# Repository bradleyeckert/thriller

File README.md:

# FPGA security stack with ROT

Root of trust for an FPGA-based device platform, built from three parts: an FPGA with an encrypted and authenticated bitstream,
one QSPI NOR flash, and a TPM 2.0 (ST33KTPM2X). The FPGA is a model of the ASIC that replaces it
at volume (`doc/ics55.md`), so everything the FPGA does is generic RTL and firmware, and everything that depends on the FPGA family lives in `fpga/<family>/`.

- **The FPGA is the root of trust and the application.** Its configuration engine authenticates and decrypts the bitstream with the device's own eFuse key;
  the bitstream holds a boot ROM, a loader core that owns every key path and security decision and is, with its hardware, the FIPS 140-3 cryptographic module; a supervisor core that
  runs the manufacturer's transports, scheduling and CLI outside the module, so that those change without a CMVP filing; and an application core that runs the LiteForth application and can reach
  nothing secret. All three execute in place from the flash through a decrypting, authenticating cache (`doc/xip.md`).
- **The TPM holds what must survive the bitstream:** the device's keys, its identity, and the two monotonic counters that stop rollback.
  It releases a key only to a bitstream that holds the current pairing key, and the data key only after the host has proved itself to the TPM directly (`doc/tpm.md`).
  It is a FIPS 140-3 validated module in its own right, which is what lets the device's own module boundary stop at the loader domain (`doc/fips.md`).
- **The flash is untrusted storage** for the bitstream, the loader, the supervisor and the application, every line of code authenticated as it is fetched (`doc/flash.md`).
- **The module is frozen.** Every change to the bitstream or the loader is a filing with the CMVP, so the loader is a crypto kernel with a fixed service API and all product logic lives in the supervisor and application images (`doc/fips.md`, Designing for few filings).

The platform will encrypt files, so the TPM is provisioned accordingly.
To support DSP applications, audio CODECs are planned for.

## Documents

| Document | Contents |
|---|---|
| This README | Overview: chipset, keys, boot, updates, recordings, sensor, host sessions, the network and the CLI |
| `doc/arch.md` | Trust boundary, threat model, risk assessment, algorithm bill of materials |
| `doc/hw.md` | Hardware modules: the three cores, the mailboxes, the shared XIP engine, key paths, boot and lockdown, the key-source interface |
| `doc/api.md` | The module's service API: mailbox messages, session messages the module consumes, events, status block, parameters carried as data |
| `doc/tpm.md` | TPM: NV indices, sealed objects and PCRs, sessions over SPI, host authentication, the pairing-key ratchet, counters, attestation, provisioning |
| `doc/flash.md` | Flash map: bitstream slots and multi-boot, loader, supervisor and application slots, boot record, install order, staging |
| `doc/fpga.md` | The FPGA, family-neutral: configuration from flash, per-device bitstreams, fallback, TRNG, resources |
| `fpga/` | Everything family-specific, one folder per FPGA family, and the wish list a family must meet |
| `doc/xip.md` | Execute in place: per-line Ascon-AEAD128 for the loader, the supervisor and the application |
| `doc/acquisition.md` | CODECs, data path, recording encryption, LCD, speaker and alarms |
| `doc/sensor.md` | Replaceable temperature sensor: certificates, offline pairing, authenticated sessions, fail-safe behavior |
| `doc/enrollment.md` | Device and sensor enrollment, TPM provisioning, the bitstream build service, detecting unknown identities, updates |
| `doc/roles.md` | Manufacturer, application owner, developer and user; device-bound developer builds |
| `doc/test.md` | Test plan and fault-injection campaigns |
| `doc/fda.md` | FDA security architecture views |
| `doc/network.md` | Network security posture: why the device cannot be a network attack vector, for IT departments and the FDA |
| `doc/fips.md` | FIPS 140-3 as the long-term target: designing for few filings, module boundary, approved algorithms, DRBG, self-tests, roles, zeroization, and what it changes now |
| `doc/ics55.md` | ASIC migration to the ICS55 55 nm process: the PUF behind the key-source interface |
| `hw/module.md` | The mezzanine module and its carrier: what is on which, what is potted, the 160-contact pinout contract, clocking, removal detection, the two carriers |
| `hw/potting.md` | What potting defends against and what it does not; Level 2 coating versus Level 3 potting; validate at Level 2 first |
| `doc/questions.md` | Every open question in one matrix, and the decisions taken |

## Module Chipset

- **FPGA with an encrypted and authenticated bitstream.** Current choice: **Pango Logos2 PG2L50H-6IMBG324** (50K-class), which authenticates bitstreams before decrypting them
  (`fpga/logos2/`). No family offers a hardened cipher usable from the fabric, so all symmetric cryptography runs in a masked Ascon core of our own (`doc/hw.md`). It configures itself from the flash at power-up in master SPI mode, with the vendor's multi-boot fallback to a second bitstream. Fallback: **Efinix Titanium Ti60** (`fpga/ti60/`), which meets the same hard requirements with RSA-4096 authentication
  and a scripted BRAM content updater. Candidates: Microchip PolarFire, Lattice CrossLink-NX. The ECP5 and Gowin GW5A were evaluated and dropped for lacking bitstream authentication. The requirements a family must meet are in `fpga/README.md`.
- **QSPI NOR flash**, 32 MB proposed: bitstream slots, loader, supervisor and application images (A/B each), the boot record and a recovery staging area (`doc/flash.md`). Nothing in it is trusted.
- **ST33KTPM2X32DKG9** TPM 2.0 (STMicroelectronics), on an SPI bus that never leaves the sealed enclosure, powered with the FPGA. Chosen over the ATECC608C when FIPS 140-3 became the target:
  it is on CMVP certificate #5570 (FIPS 140-3, physical security Level 3), ships with ST-certified endorsement keys, and sits inside the device's own module boundary as an embedded validated
  module, so its services need no testing of ours (`doc/fips.md`). Keys are sealed objects released only under a policy that names the pairing key; counters are its NV counters, authenticated and
  authorized; its indices cannot be deleted by anyone but the enrollment station (`doc/tpm.md`).
  Provisioned blank at enrollment.
- **ESP-PSRAM64H** (8 MB QSPI PSRAM): a ring buffer for the encrypted recording stream between the recording engine and the card or the network, riding out card write latency and network stalls.
- **YXC YSN8130E real-time clock** (3225 module with built-in crystal, 0.9 µA, open-drain /INT that survives a VDD cycle); A10 for the remaining checks. Its time is untrusted and never stands in for the server's time beacons (`doc/acquisition.md`); its job is
  scheduling and local display, and **its alarm output wakes the device from deep sleep** (the regulators' enables on the FPGA board, RST_N on the ASIC), so every scheduled wake is a cold start through the
  entire trust chain; the alarm is also an input pin, so the supervisor sees it as an interrupt when awake. It also automates NIST SP 800-90B restart testing of the TRNG: a thousand wakes, each logging its first raw samples (`doc/hw.md`, Real-time clock).
- **Ethernet PHY**, RMII such as the LAN8742A: the path to the server for attestation, updates, uploads and sensor-pairing confirmation. The FPGA speaks only UDP on one port,
  implemented in hardware; there is no network stack anywhere in the device (see Network). An untrusted edge proxy on site relays the datagrams to the server over TLS where IT requires port 443.
- **25 MHz oscillator** clocks both PHY and FPGA
- Voltage regulators, bypass caps, etc.
- Mezzanine module, 20 mm wide by about 40 mm, with two DF40C-80DP-0.4V(51) connectors (160 contacts) to the carrier (`hw/module.md`).

## Application peripherals

Each FPGA version will have its own version of module with mezzanine connectors.
The module contains the chipset. The carrier board contains everything else:

- **5V input** from **USB-C jack**.
- **MicroSD card socket**, driven by the FPGA: encrypted recordings and user data, the event log, offline update packages.
- **FT2232H** (USB-UART bridge and JTAG): status reports, and the wired path for host sessions, updates and the CLI.
- **Battery holder** for two SR44 cells (not CR2032, lithium is a shipping hassle)
- **Ethernet Jack**, 10/100 mag jack RJ45
- **MicroSD** card socket with TVS on all data lines
- **Sensor connector**: a wired, two-way link to a replaceable temperature sensor; the supervisor moves the bytes, the module checks every frame (`doc/sensor.md`).
- **2 × NAU88C22** stereo CODECs: four acquisition channels, and the speaker driver (`doc/acquisition.md`).
- **SI5351A-B-GTR** precision clock generator. Use a 25 MHz crystal.
- **Freq reference input**: 10 MHz reference input to FPGA, with Schmitt-trigger squaring.
- **speaker** with amplifier, may use simple PWM.
- **LCD panel** with touch panel (I2C) and 4-wire SPI LCD controller.

Treat these components as if they are either inside or sticking through a tamper-evident enclosure.

## Keys and what unlocks them

| Key | Held in | Per device | Unlocked by | Protects |
|---|---|---|---|---|
| Bitstream configuration key | FPGA eFuse; HSM | Yes | The FPGA alone | The bitstream at rest in flash and on the configuration bus |
| Bitstream signing key | Manufacturer HSM; public key data in FPGA eFuse | No | — | Only manufacturer bitstreams configure the FPGA (where the family authenticates) |
| **Pairing key** | The bitstream (key source) and the TPM's pairing index, as its authorization value | Yes, and per bitstream release | The bitstream itself | Every TPM session: the session key, every HMAC, every policy. Rotated with each bitstream release, which is what kills old bitstreams (`doc/tpm.md`, Ratchet) |
| Application key | TPM, sealed | Yes | Pairing key | Headers and per-line keys of the loader, supervisor and application images in flash; the boot record |
| **Data key** | TPM, sealed, one per host | Yes | Pairing key **and** the host's proof to the TPM (a relayed HMAC session) | User data on the MicroSD card |
| Host authorization key | TPM (an NV index's authorization value, never readable) and the host | Yes, per host | Never leaves either | Proving the host is present; the host session secret sealed with the data key derives the session key |
| Device identity key (symmetric) | TPM (keyed-hash object, never readable); HSM | Yes | Pairing key; used in place | Authenticating the device to the enrollment server, quantum-safe |
| Attestation key (ECDSA P-256) | TPM (never readable); certificate chained to the manufacturer CA, bound to ST's endorsement key certificate | Yes | Pairing key | Quotes over the PCRs for hosts and third parties |
| Distribution key | TPM, sealed | No | Pairing key | Production application packages in transit; a device never enrolled cannot install them |
| Developer key | TPM, sealed | Yes | Pairing key, into hardware only | Developer builds for that one device (`doc/roles.md`) |
| Log key | TPM, sealed | Yes | Pairing key | The security event log's MAC chain |
| Release LMS keys (platform; application), main and backup | HSMs; platform public key in the boot ROM, application keys in write-locked TPM NV | No | — | Every update package, checked before anything is decrypted or installed |
| Host data secret | Host only; from a separate HSM master | Yes | — | Unlocks user data together with the device's data key |
| Host recording key pair (ML-KEM-768) | Private key on the host; public key in flash, under the application key | Per host | — | Recordings: the device can encrypt them but not decrypt them |
| Segment key | Loader domain and the recording engine, for one segment, then erased | Per segment | — | One segment of a recording |
| Sensor pairing key | Flash (under the application key) and the sensor | Per pairing | — | Sessions with one paired sensor |

The HSM derives every per-device key from a master key and the TPM's identifier (`doc/enrollment.md`). No stored key ever reaches software on any core: keys move from the
TPM or the key source into hardware key registers (`doc/hw.md`, Key paths). The one computed secret that does pass through loader software is the ML-KEM shared secret, which the
encapsulation code produces and hands to the derive path (H10).

## Boot

1. The FPGA's configuration engine loads the active bitstream from flash, checks its signature and decrypts it with the device's eFuse key; anything else is refused. On failure it falls back to the other
   bitstream slot (the family's multi-boot).
2. The **boot ROM** (block RAM in the bitstream) starts on the loader core with the other two cores in reset. It starts the TPM, opens a session under the pairing key, reads counter 0,
   has the TPM unseal the application key, checks the loader image's header and version, derives the loader's image key into the XIP engine, and jumps to the loader in flash.
   If the TPM refuses the pairing key, this bitstream has been superseded: the boot ROM stops in recovery.
3. The **loader** reads counters 1 and 2, checks the supervisor image's header and version, then the application's (or, for a developer build, device and epoch), derives their image keys,
   applies the network policy to the PHY's reset, and releases the supervisor core, then the application core. Every cache line of every image is authenticated as it is fetched.
4. The **supervisor** brings up the card, the clock, the schedule and, if the policy allows, the network address, and has the module open the sensor session.
5. The application runs. It reaches user data, recordings, the host, the sensor and the log only through the module's services; the supervisor moves the bytes.

Any check that fails falls back to the other slot of that image, or stops in the safe state with a record in the boot record (`doc/hw.md`, Boot and lockdown).

## Updates

Two signed chains, sharing nothing but the TPM:

| Package | Contents | Scope | Signed by | Counter |
|---|---|---|---|---|
| Platform | This device's encrypted bitstream with its next pairing key, and a loader image | Per device, built by the bitstream build service | LMS (manufacturer), one signature per release over a manifest | 0 |
| Supervisor | The manufacturer's supervisor image: transports, scheduling, CLI | Fleet | LMS (manufacturer) | 2 |
| Application | The LiteForth application, and its network policy | Fleet; encrypted under the distribution key | LMS (application owner); developer builds: a MAC under the device's developer key | 1 |

Packages arrive on the MicroSD card, over the UART from the host, or over the network, and the supervisor streams them to the module. The module checks the signature and the version before decrypting anything, writes into the
inactive slot, reads it back, advances the counter and switches the boot record (`doc/flash.md`, Install order). A bitstream update ends with the new bitstream, once it has booted,
replacing the pairing key in the TPM with its next key, after which the old bitstream can no longer open the TPM. Platform packages are the rare ones: each is a change to the FIPS module and a CMVP filing; supervisor and application packages are not (`doc/fips.md`).

## Recordings

The loader draws a fresh key for each segment, encapsulates it with ML-KEM to the host's public key, and loads it into the recording engine, which encrypts the stream in the FPGA's
masked Ascon core and writes ciphertext to the card. The segment key is then erased, so the device cannot read its own past recordings, and neither can a thief (`doc/acquisition.md`).

## Sensor

The temperature sensor is replaceable and pairs offline with an ML-DSA certificate and ML-KEM. Every frame carries a MAC, readings older than the maximum age are rejected,
and the server later confirms each pairing and catches clones (`doc/sensor.md`).

## Host sessions and user data

The host proves itself to the TPM, not to the loader: the loader relays one TPM command's HMAC, which the host computes under its own key, and the TPM unseals the data key only when it
verifies; the host session secret unsealed alongside derives the session key, so that every frame is encrypted and authenticated. User data other than recordings is encrypted under a key derived from both the device's data key and a secret the host sends in each
session, which the device never stores. A lost host is re-issued from the HSM. A compromised host means retiring the device (`doc/arch.md`, R20).

## Attestation and identity

The device proves what it is and what it runs in two ways (`doc/tpm.md`, Attestation):

- to the enrollment server, with a MAC under its symmetric identity key over the server's nonce and a report of its versions and counters: quantum-safe, and the HSM can derive the key;
- to a host or a third party, with a TPM quote: an ECDSA P-256 signature over PCRs the loader extended with the same report, under a per-device attestation key certificate chained to the manufacturer's CA and to ST's endorsement key certificate.

The TPM signs only for a bitstream that holds the current pairing key, so a report proves the pairing, the bitstream release, and the versions the loader measured.

## Network and the CLI

There are no radios. The device has one wired Ethernet port, and the FPGA implements the whole of its network side in hardware (`doc/hw.md`, Ethernet transport): an RMII MAC, an ARP
responder for its own address, IPv4 without fragments or options, ICMP echo, and a UDP demultiplexer that delivers datagrams on one port to the supervisor core and drops everything else.
The payload is the same authenticated, encrypted session frame the module already checks from the UART, so the network is a second transport for one protocol, with no TCP, DNS, TLS or HTTP
anywhere in the device. Flows are outbound only, with keepalives; the ack-and-window layer that makes updates and uploads reliable over a lossy path is part of the session protocol.

Where a site's IT policy only allows TCP on port 443, a small **edge proxy** (software on a PC or a gateway appliance on the same LAN) relays the device's datagrams to the server over TLS.
It is outside the trust boundary and sees only ciphertext: it can drop, delay or replay, and every one of those is already handled by the session protocol.

**The application owner decides** whether the port is enabled, through a network policy in the signed application package; the module holds the PHY in reset when it is disabled, and the supervisor cannot override it.
Addressing is by DHCP, with static addresses settable in a host session; the server (or proxy) address is set the same way.

- **The UART** gives read-only status to anyone with a cable, and authenticated sessions.
- **The network** carries authenticated sessions with the server, and with a host on the same LAN.

| Session | Commands |
|---|---|
| None (UART status only) | Versions, build mode, faults, pairing state |
| Host (host authorization key) | User data, recordings, sensor pairing, updates, log export, network settings, attestation |
| Developer (developer key, developer builds only) | The above, plus the application's debug commands |

The PHY choice, PoE and the edge proxy are open items (`doc/questions.md`, A6 to A9).

## ASIC conversion

The ASIC keeps the boot ROM (now mask ROM), the loader, the supervisor and application chains, the TPM and the flash, and loses the bitstream. The one thing the bitstream carried,
the pairing key, comes instead from a PUF behind the same key-source interface the FPGA build already uses, with the hardware to characterize it on silicon (`doc/ics55.md`).

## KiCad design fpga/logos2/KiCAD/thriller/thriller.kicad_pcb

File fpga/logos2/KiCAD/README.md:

# KiCad: Logos2 symbols and the thriller module schematic

| Path | Contents |
|---|---|
| `FPGA_Pango_Logos2.kicad_sym` | Symbols for PG2L50H-6IFBG484 (earlier choice) and **PG2L50H-6IMBG324** (current). The 324 has eight units: banks L3, L4, L5, R4, R5; configuration/JTAG/ADC; core and auxiliary power; ground. Generated from `../pinout324.json` (ball → bank, pin name, pair) taken from the PK04006 pinout |
| `../pinout324.json` | Ball table of the 324 package |
| `../pinout324-assignment.csv` | Every ball with the net the module schematic puts on it (generated) |
| `thriller/` | **The module schematic** (`hw/module.md`): what is on the potted 20 × 40 mm card and nothing else |
| `tools/` | The scripts that produced the module schematic from the earlier one-board project, and the pinout tables |

## The module schematic (`thriller/`)

KiCad 9 format (version 20250114); KiCad 10 opens it and converts on save. Rev 0.2. Sheets:

| Sheet | File | Contents |
|---|---|---|
| Root | `thriller.kicad_sch` | Title, notes, the sheet symbols |
| Power | `th_power.kicad_sch` (A3) | 5 V from J1, PTC and TVS, 3V3_AO LDO, 1V0/1V8/3V3 bucks, power control from `PB_N_AO` and `RTC_INT_N_AO`; the YSN8130E RTC; the FPGA's configuration/JTAG/ADC, core-power and ground units with their straps and decoupling |
| Base | `th_base.kicad_sch` | QSPI NOR flash, **ST33KTPM2X TPM** (SPI per DB5174 figure 3: RST pull-down, PIRQ pull-up, optional 56 pF on CS and 33 Ω series), ESP-PSRAM64H |
| FPGA banks | `th_userA.kicad_sch` (A3) | Units L3, L4, L5, R4, R5 with their nets as global labels; bank decoupling |
| Ethernet PHY | `th_ext.kicad_sch` | LAN8742A on RMII with the **25 MHz oscillator** (`SYS_CLK`, the module's only clock); MDI pairs and LED lines go to J1 |
| Module connectors | `th_conn.kicad_sch` | J1 and J2, Hirose DF40C-80DP-0.4V(51); the pinout is `hw/module-pinout.csv`, regenerated from this sheet by `tools/pinout_csv.py` |

What left the board when it became a module (all of it is now the carrier's): the USB-C and CH340N bridge, the two NAU88C22 CODECs and their jacks, the LCD and touch connector, the speaker driver,
the MicroSD socket, the RJ45 and magnetics, the sensor connector and its power switch, the SI5351A, the pushbutton and enclosure switch, the backup cells, the 5 V input jack and switched 5 V rail.
What was added: the two DF40 connectors, the TPM, the 25 MHz oscillator in place of the 24 MHz one and the PHY crystal.

### Bank assignment (324)

| Bank | Rail | What is on it |
|---|---|---|
| L5 (configuration) | 3V3 | QSPI flash data and `CS` (fixed-function balls), TPM SPI, PSRAM, RTC I2C and interrupt, `SYS_CLK` on the GSCLK ball |
| L4 | 3V3 | I2S × 2, LCD, touch interrupt, the carrier I2C (`SDA`/`SCL`), speaker PWM, the two carrier clocks on clock-capable balls, GPIO0..13 |
| L3 | 3V3 | GPIO32..41 (all ten of its I/O, the two VREF balls included; 3.3 V LVCMOS needs no VREF) |
| R4 | 3V3 | PHY RMII with `ETH_REFCLK` on the GSCLK ball, SD, host UART, sensor link, pushbutton, tamper, seal loop, `PWR_HOLD`, `PGOOD` |
| R5 | 3V3 | GPIO14..31 and GPIO42..59 (its VREF and clock-capable balls left free) |
| configuration | — | Straps, JTAG, `CFG_*`, `VCCB`, `VCCADC`, `ADC_5V_MON`, all on `th_power` |

The loader domain's pins (flash, TPM, PSRAM, RTC, the clock) are all on L5 so the partition's I/O stays inside one bank (`doc/fips.md`, F12).

### Things to check before layout

- The 3V3 rail's rise time at the TPM: DB5174 table 4 wants 2 V/ms or faster (H14).
- H15: LAN8742A REF_CLK Out mode with an external 25 MHz clock on XTAL1.
- Four stub wires on `th_userA` bank L4 (balls B13, B12, D12, B17) end in nothing; give them a net or a no-connect.
- The core decoupling quantities (now on `th_power`) against UG040012 tables 2-3 and 2-6 for the 324 package.
- `thriller_bom.csv` is from the one-board revision and is stale; regenerate from the schematic.

## tools/

| Script | What it does |
|---|---|
| `ksch.py` | Minimal KiCad 9 schematic s-expression toolkit: parse, serialize, pin geometry, net connectivity |
| `rework_module.py` | The one-board → module transformation of 2026-11-18 (its output was commit f718401; the schematic has been rearranged by hand since, so it is history, not a generator). Runs on the one-board revision (`git checkout f718401^ -- thriller`), reproducibly |
| `label_shapes.py` | Sets every global label's shape (input/output/bidirectional, the direction relative to the sheet it is on, from a per-net table of what the parts do) and 45 mil text. By default it only fills in labels still marked passive and keeps hand-set shapes; `--check` reports, `--force` applies the table everywhere |
| `edit_pins.py` | Text-level pin edits that keep eeschema's formatting (remove or add a global label with its stub, add or remove a no-connect); its `main` is the 2026-11-20 move of GPIO32..59 onto L3/R5 and the removal of `SENS_DET`, `SENS_27M`, `CARRIER_ID` |
| `pinout_csv.py` | Regenerates `hw/module-pinout.csv` from `th_conn` and the FPGA units (contact, net, ball, bank from the schematic; group, class and note kept from the existing CSV by net name), and `../pinout324-assignment.csv`. `--check` reports differences without writing |
| `render_sch.py` | Rough SVG/PNG preview of a sheet for checking generated geometry without KiCad |

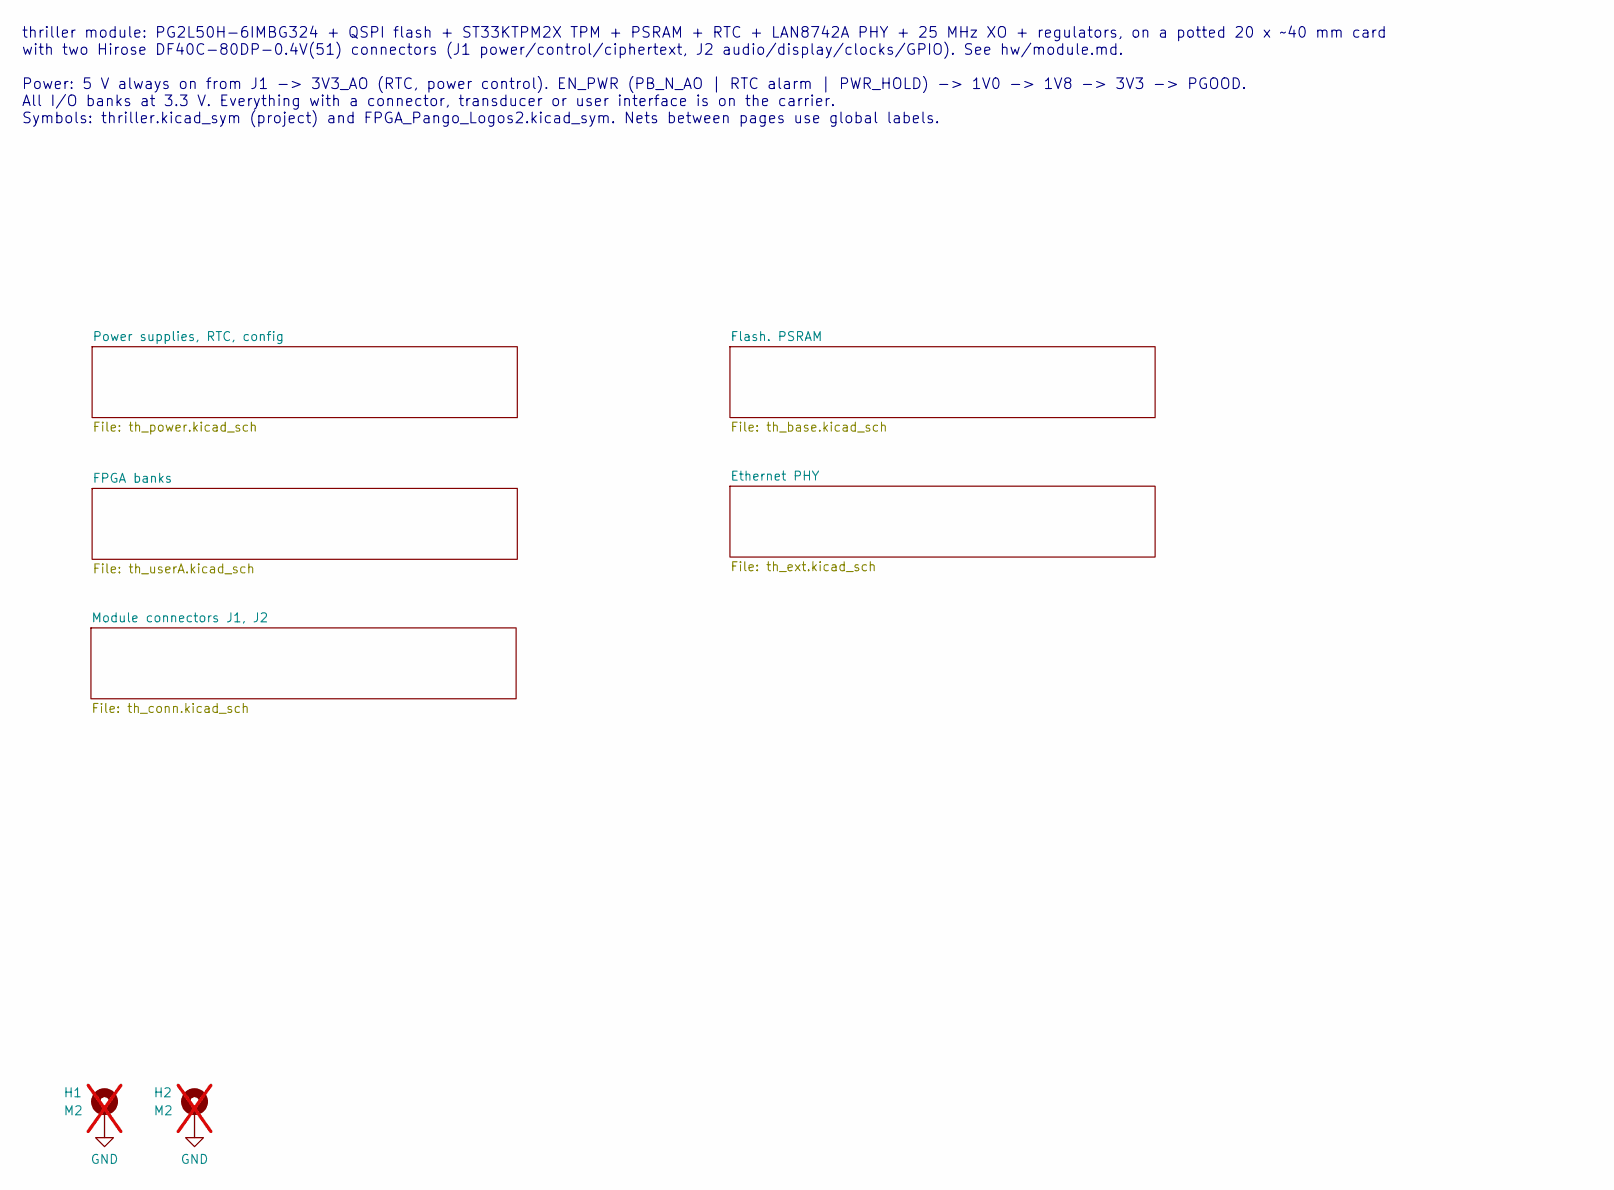
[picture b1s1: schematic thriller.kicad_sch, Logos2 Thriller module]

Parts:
H1, H2: M2; MountingHole_2.2mm_M2_DIN965_Pad_TopBottom; not fitted

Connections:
GND: H1.1 (1_1), H2.1 (1_1); also elsewhere on the board

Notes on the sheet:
thriller module: PG2L50H-6IMBG324 + QSPI flash + ST33KTPM2X TPM + PSRAM + RTC + LAN8742A PHY + 25 MHz XO + regulators, on a potted 20 x ~40 mm card with two Hirose DF40C-80DP-0.4V(51) connectors (J1 power/control/ciphertext, J2 audio/display/clocks/GPIO). See hw/module.md. Power: 5 V always on from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

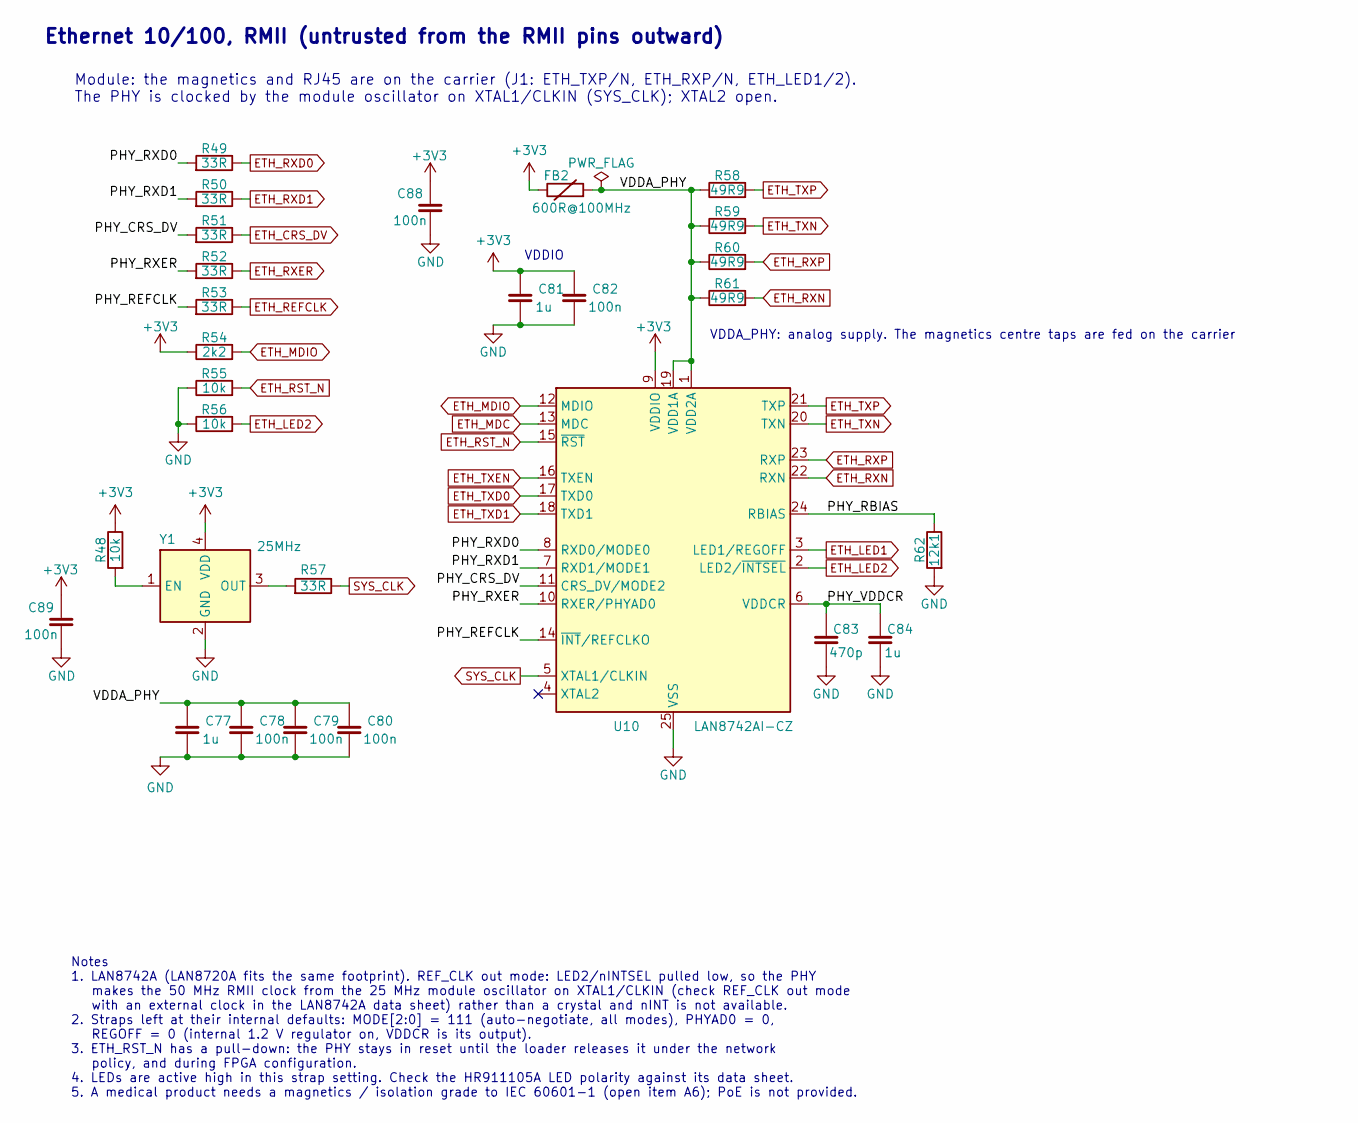
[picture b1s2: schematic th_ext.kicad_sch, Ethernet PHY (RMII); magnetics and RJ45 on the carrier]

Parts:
C77, C81, C84: 1u; C_0402_1005Metric; LCSC C52923
C78, C79, C80, C82, C88, C89: 100n; C_0402_1005Metric; LCSC C1525
C83: 470p; C_0402_1005Metric
FB2: 600R@100MHz; L_0603_1608Metric; MPN GZ1608D601TF; LCSC C1002
R48, R55, R56: 10k; R_0402_1005Metric; LCSC C25744
R49, R50, R51, R52, R53, R57: 33R; R_0402_1005Metric; LCSC C25105
R54: 2k2; R_0402_1005Metric; LCSC C25879
R58, R59, R60, R61: 49R9; R_0402_1005Metric; LCSC C25120
R62: 12k1; R_0402_1005Metric
U10: LAN8742AI-CZ; QFN-24-1EP_4x4mm_P0.5mm_EP2.6x2.6mm; MPN LAN8742AI-CZ-TR; LCSC C621425
Y1: 25MHz; Oscillator_SMD_Abracon_ASE-4Pin_3.2x2.5mm; MPN 25 MHz 3225 CMOS XO, 3.3 V (choose LCSC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

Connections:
/Ethernet PHY/PHY_CRS_DV: R51.1, U10.11 (CRS_DV/MODE2)
/Ethernet PHY/PHY_RBIAS: R62.2, U10.24 (RBIAS)
/Ethernet PHY/PHY_REFCLK: R53.1, U10.14 (~INT/REFCLKO)
/Ethernet PHY/PHY_RXD0: R49.1, U10.8 (RXD0/MODE0)
/Ethernet PHY/PHY_RXD1: R50.1, U10.7 (RXD1/MODE1)
/Ethernet PHY/PHY_RXER: R52.1, U10.10 (RXER/PHYAD0)
/Ethernet PHY/PHY_VDDCR: C83.1, C84.1, U10.6 (VDDCR)
/Ethernet PHY/VDDA_PHY: C77.1, C78.1, C79.1, C80.1, FB2.1, R58.2, R59.2, R60.2, R61.2, U10.1 (VDD2A), U10.19 (VDD1A)
ETH_CRS_DV: R51.2; also elsewhere on the board
ETH_LED1: U10.3 (LED1/REGOFF); also elsewhere on the board
ETH_LED2: R56.1, U10.2 (LED2/~INTSEL); also elsewhere on the board
ETH_MDC: U10.13 (MDC); also elsewhere on the board
ETH_MDIO: R54.1, U10.12 (MDIO); also elsewhere on the board
ETH_REFCLK: R53.2; also elsewhere on the board
ETH_RST_N: R55.1, U10.15 (~RST); also elsewhere on the board
ETH_RXD0: R49.2; also elsewhere on the board
ETH_RXD1: R50.2; also elsewhere on the board
ETH_RXER: R52.2; also elsewhere on the board
ETH_RXN: R61.1, U10.22 (RXN); also elsewhere on the board
ETH_RXP: R60.1, U10.23 (RXP); also elsewhere on the board
ETH_TXD0: U10.17 (TXD0); also elsewhere on the board
ETH_TXD1: U10.18 (TXD1); also elsewhere on the board
ETH_TXEN: U10.16 (TXEN); also elsewhere on the board
ETH_TXN: R59.1, U10.20 (TXN); also elsewhere on the board
ETH_TXP: R58.1, U10.21 (TXP); also elsewhere on the board
GND: C77.2, C78.2, C79.2, C80.2, C81.2, C82.2, C83.2, C84.2, C88.2, C89.2, R55.2, R56.2, R62.1, U10.25 (VSS), Y1.2 (GND); also elsewhere on the board
unnamed: R48.1, Y1.1 (EN)
unnamed: R57.1, Y1.3 (OUT)
SYS_CLK: R57.2, U10.5 (XTAL1/CLKIN); also elsewhere on the board

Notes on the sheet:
Module: the magnetics and RJ45 are on the carrier (J1: ETH_TXP/N, ETH_RXP/N, ETH_LED1/2). The PHY is clocked by the module oscillator on XTAL1/CLKIN (SYS_CLK); XTAL2 open.
Ethernet 10/100, RMII (untrusted from the RMII pins outward)
Notes 1. LAN8742A (LAN8720A fits the same footprint). REF_CLK out mode: LED2/nINTSEL pulled low, so the PHY makes the 50 MHz RMII clock from the 25 MHz module oscillator on XTAL1/CLKIN (check REF_CLK out mode with an external clock in the LAN8742A data sheet) rather than a crystal and nINT is not a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
VDDIO
VDDA_PHY: analog supply. The magnetics centre taps are fed on the carrier

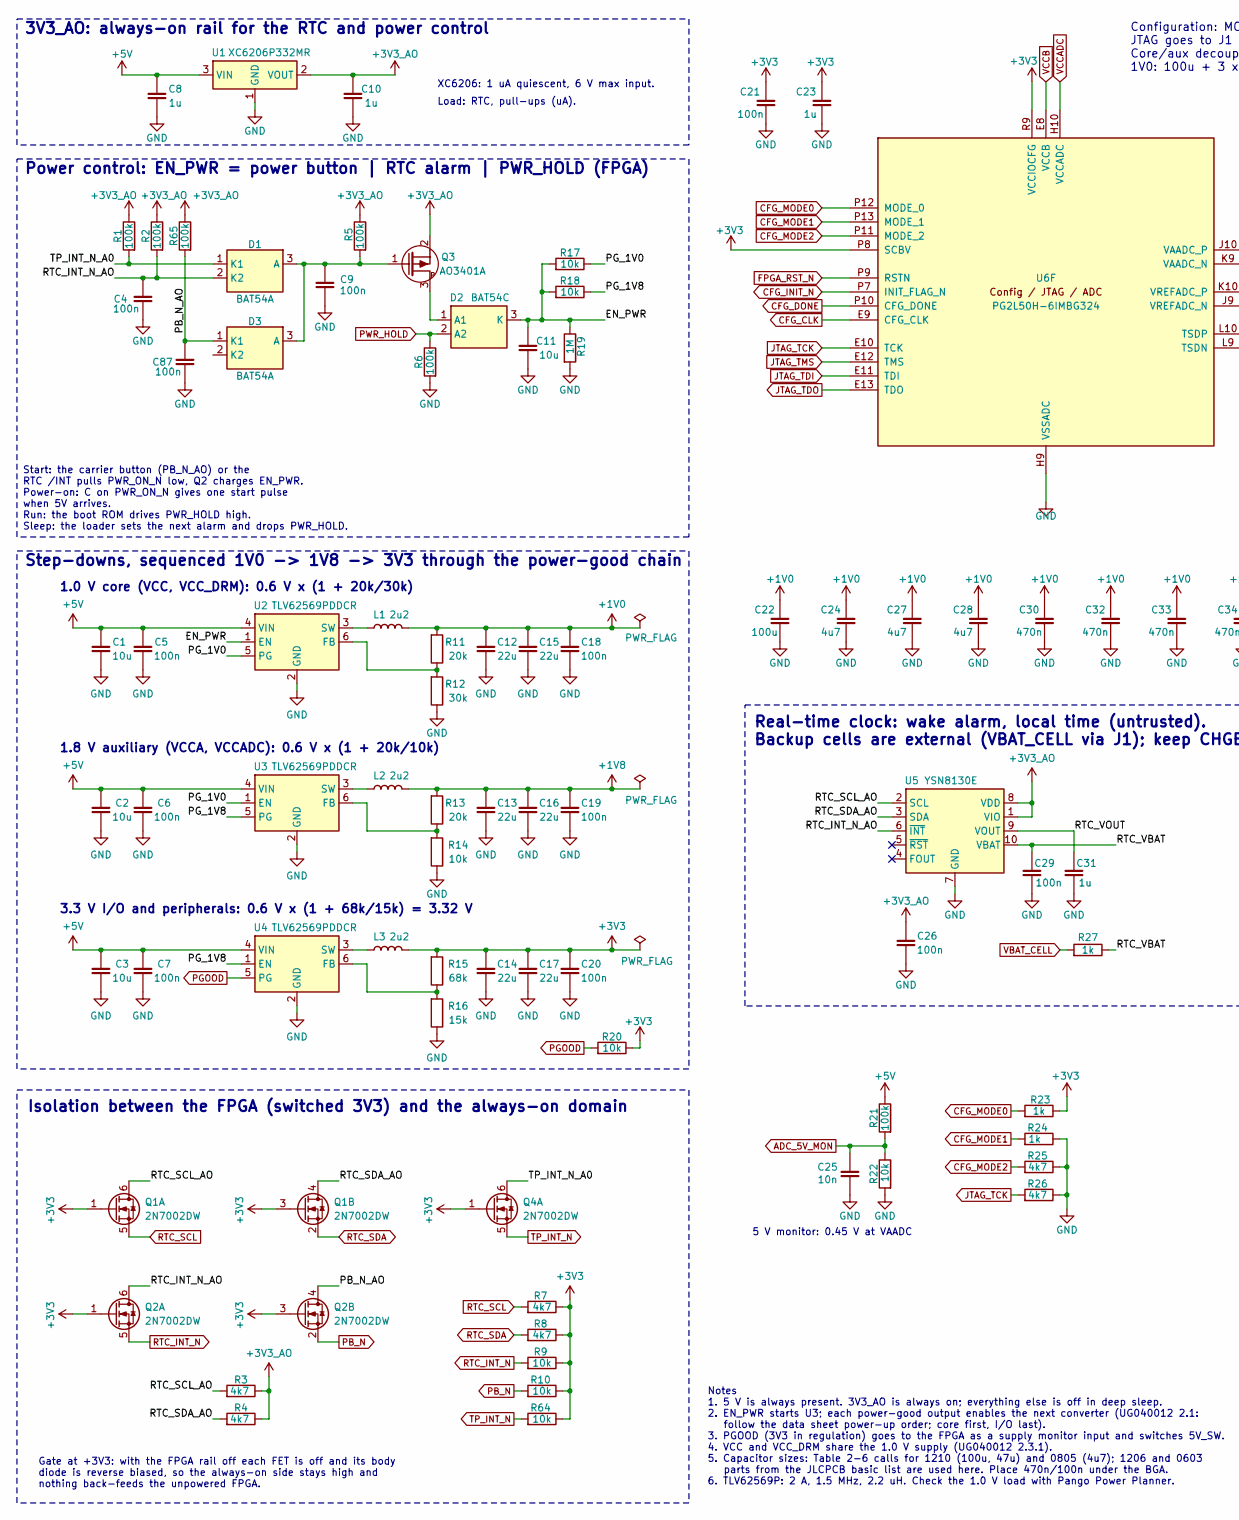
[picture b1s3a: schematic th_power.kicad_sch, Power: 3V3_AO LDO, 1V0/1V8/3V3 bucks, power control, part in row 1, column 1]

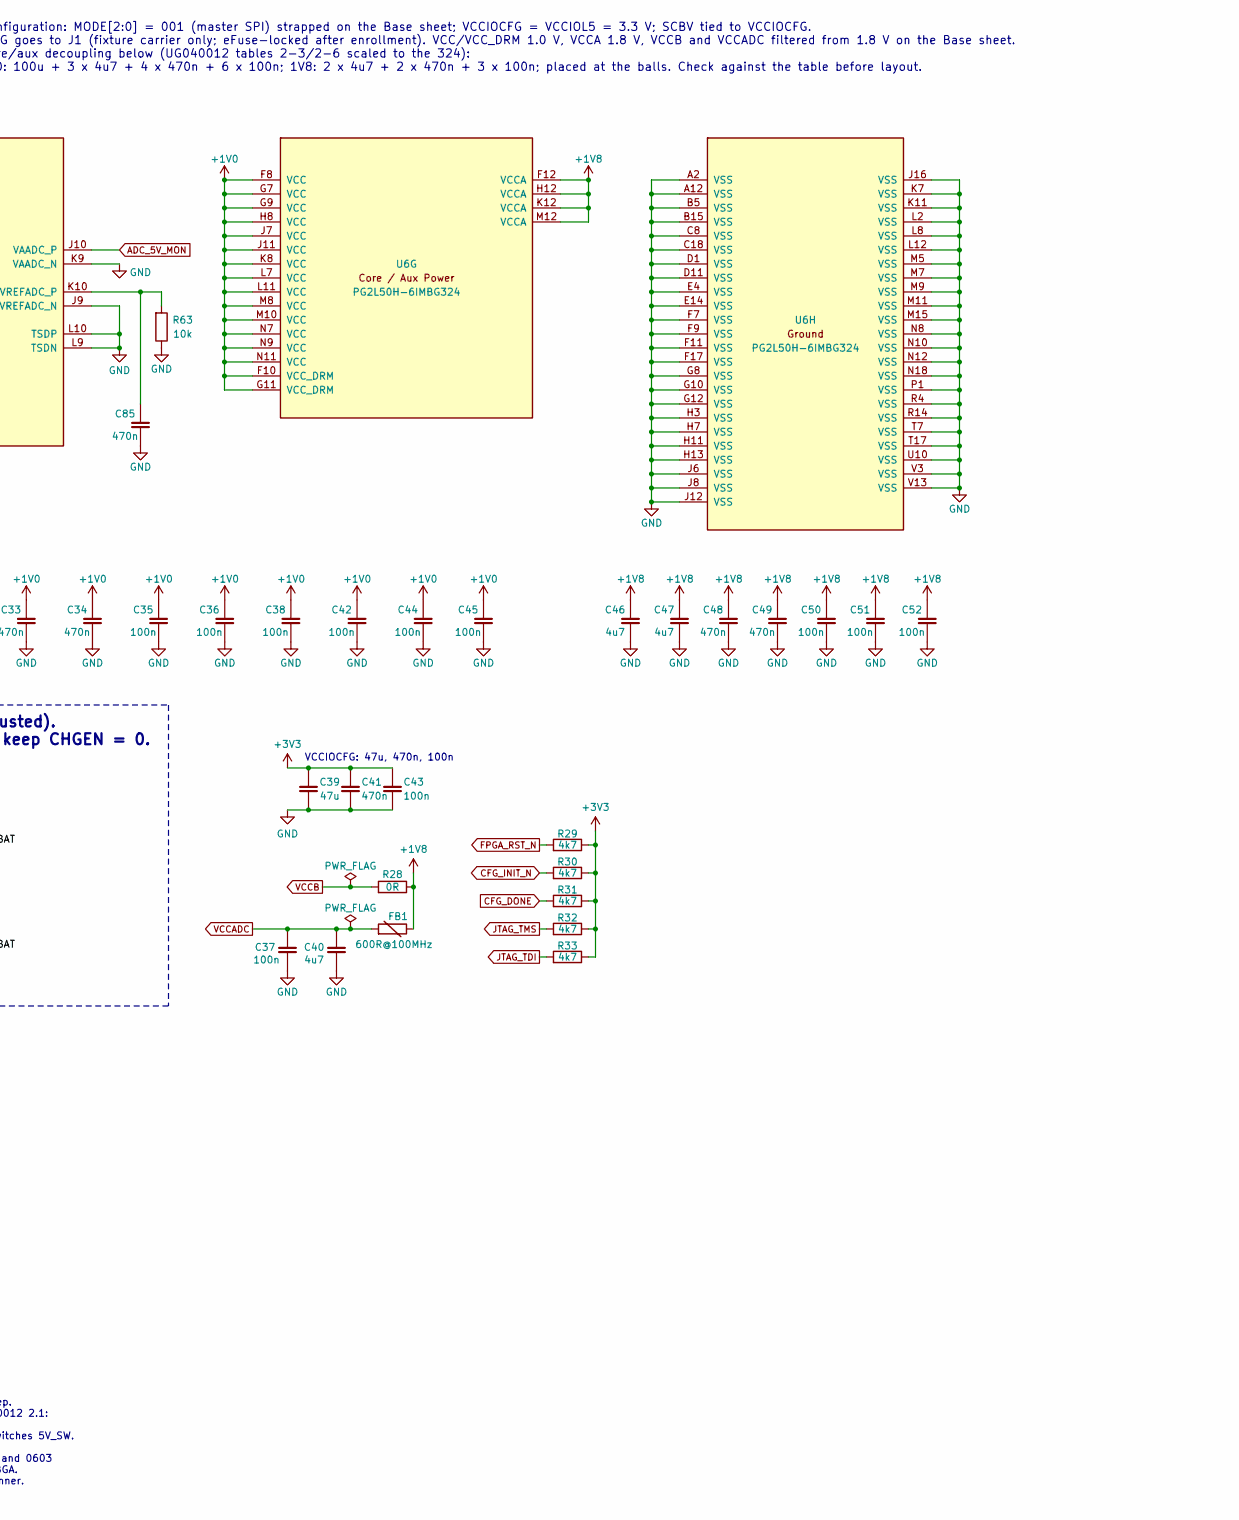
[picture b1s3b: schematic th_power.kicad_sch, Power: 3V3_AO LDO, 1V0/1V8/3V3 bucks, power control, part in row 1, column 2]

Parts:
C1, C2, C3, C11: 10u; C_0603_1608Metric; LCSC C19702
C4, C5, C6, C7, C9, C18, C19, C20, C21, C26, C29, C35, C36, C37, C38, C42, C43, C44, C45, C50, C51, C52, C87: 100n; C_0402_1005Metric; LCSC C1525
C8, C10, C23, C31: 1u; C_0402_1005Metric; LCSC C52923
C12, C13, C14, C15, C16, C17: 22u; C_0805_2012Metric; LCSC C45783
C22: 100u; C_1206_3216Metric; LCSC C15008
C24, C27, C28, C40, C46, C47: 4u7; C_0603_1608Metric; LCSC C19666
C25: 10n; C_0402_1005Metric; LCSC C15195
C30, C32, C33, C34, C41, C48, C49, C85: 470n; C_0402_1005Metric
C39: 47u; C_1206_3216Metric; LCSC C96123
D1, D3: BAT54A; SOT-23; MPN BAT54A
D2: BAT54C; SOT-23; MPN BAT54C
FB1: 600R@100MHz; L_0603_1608Metric; MPN GZ1608D601TF; LCSC C1002
L1, L2, L3: 2u2; L_Sunlord_SWPA4030S; MPN SWPA4030S2R2MT
Q1, Q2, Q4: 2N7002DW; SOT-363_SC-70-6; MPN 2N7002DW
Q3: AO3401A; SOT-23; MPN AO3401A; LCSC C15127
R1, R2, R5, R6, R21, R65: 100k; R_0402_1005Metric; LCSC C25741
R3, R4, R7, R8, R25, R26, R29, R30, R31, R32, R33: 4k7; R_0402_1005Metric; LCSC C25900
R9, R10, R14, R17, R18, R20, R22, R63, R64: 10k; R_0402_1005Metric; LCSC C25744
R11, R13: 20k; R_0402_1005Metric; LCSC C25765
R12: 30k; R_0402_1005Metric
R15: 68k; R_0402_1005Metric
R16: 15k; R_0402_1005Metric; LCSC C25756
R19: 1M; R_0402_1005Metric; LCSC C26083
R23, R24, R27: 1k; R_0402_1005Metric; LCSC C11702
R28: 0R; R_0402_1005Metric; LCSC C17168
U1: XC6206P332MR; SOT-23; MPN XC6206P332MR; LCSC C5446
U2, U3, U4: TLV62569PDDCR; TSOT-23-6; MPN TLV62569PDDCR; LCSC C398365
U5: YSN8130E; RTC_Epson_CE_SMD-10P_3.2x2.5mm_P0.7mm; MPN YSN8130E; LCSC C48888238
U6: PG2L50H-6IMBG324; BGA-324_15x15mm_Layout18x18_P0.8mm; MPN PG2L50H-6IMBG324

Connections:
+3V3_AO: C10.1, C26.1, Q3.2 (S), R1.2, R2.2, R3.2, R4.2, R5.2, R65.2, U1.2 (VOUT), U5.1 (VIO), U5.8 (VDD)
+5V: C1.1, C2.1, C3.1, C5.1, C6.1, C7.1, C8.1, R21.2, U1.3 (VIN), U2.4 (VIN), U3.4 (VIN), U4.4 (VIN); also elsewhere on the board
/Power supplies, RTC, config/EN_PWR: C11.1, D2.3 (K), R17.1, R18.1, R19.2, U2.1 (EN)
/Power supplies, RTC, config/PB_N_AO: C87.2, D3.1 (K1), Q2.4 (D), R65.1
/Power supplies, RTC, config/PG_1V0: R17.2, U2.5 (PG), U3.1 (EN)
/Power supplies, RTC, config/PG_1V8: R18.2, U3.5 (PG), U4.1 (EN)
/Power supplies, RTC, config/RTC_INT_N_AO: C4.2, D1.2 (K2), Q2.6 (D), R2.1, U5.6 (~INT)
/Power supplies, RTC, config/RTC_SCL_AO: Q1.6 (D), R3.1, U5.2 (SCL)
/Power supplies, RTC, config/RTC_SDA_AO: Q1.4 (D), R4.1, U5.3 (SDA)
/Power supplies, RTC, config/RTC_VBAT: C29.1, R27.2, U5.10 (VBAT)
/Power supplies, RTC, config/RTC_VOUT: C31.1, U5.9 (VOUT)
/Power supplies, RTC, config/TP_INT_N_A0: D1.1 (K1), Q4.6 (D), R1.1
ADC_5V_MON: C25.1, R21.1, R22.2, U6.J10 (VAADC_P)
CFG_CLK: U6.E9 (CFG_CLK); also elsewhere on the board
CFG_DONE: R31.1, U6.P10 (CFG_DONE)
CFG_INIT_N: R30.1, U6.P7 (INIT_FLAG_N)
CFG_MODE0: R23.1, U6.P12 (MODE_0)
CFG_MODE1: R24.1, U6.P13 (MODE_1)
CFG_MODE2: R25.1, U6.P11 (MODE_2)
FPGA_RST_N: R29.1, U6.P9 (RSTN)
GND: C1.2, C2.2, C3.2, C4.1, C5.2, C6.2, C7.2, C8.2, C9.1, C10.2, C11.2, C12.2, C13.2, C14.2, C15.2, C16.2, C17.2, C18.2, C19.2, C20.2, C21.2, C22.2, C23.2, C24.2, C25.2, C26.2, C27.2, C28.2, C29.2, C30.2, C31.2, C32.2, C33.2, C34.2, C35.2, C36.2, C37.1, C38.2, C39.2, C40.1, C41.2, C42.2, C43.2, C44.2, C45.2, C46.2, C47.2, C48.2, C49.2, C50.2, C51.2, C52.2, C85.2, C87.1, R6.1, R12.2, R14.2, R16.2, R19.1, R22.1, R24.2, R25.2, R26.2, R63.2, U1.1 (GND), U2.2 (GND), U3.2 (GND), U4.2 (GND), U5.7 (GND), U6.A2 (VSS), U6.A12 (VSS), U6.B5 (VSS), U6.B15 (VSS), U6.C8 (VSS), U6.C18 (VSS), U6.D1 (VSS), U6.D11 (VSS), U6.E4 (VSS), U6.E14 (VSS), U6.F7 (VSS), U6.F9 (VSS), U6.F11 (VSS), U6.F17 (VSS), U6.G8 (VSS), U6.G10 (VSS), U6.G12 (VSS), U6.H3 (VSS), U6.H7 (VSS), U6.H9 (VSSADC), U6.H11 (VSS), U6.H13 (VSS), U6.J6 (VSS), U6.J8 (VSS), U6.J9 (VREFADC_N), U6.J12 (VSS), U6.J16 (VSS), U6.K7 (VSS), U6.K9 (VAADC_N), U6.K11 (VSS), U6.L2 (VSS), U6.L8 (VSS), U6.L9 (TSDN), U6.L10 (TSDP), U6.L12 (VSS), U6.M5 (VSS), U6.M7 (VSS), U6.M9 (VSS), U6.M11 (VSS), U6.M15 (VSS), U6.N8 (VSS), U6.N10 (VSS), U6.N12 (VSS), U6.N18 (VSS), U6.P1 (VSS), U6.R4 (VSS), U6.R14 (VSS), U6.T7 (VSS), U6.T17 (VSS), U6.U10 (VSS), U6.V3 (VSS), U6.V13 (VSS); also elsewhere on the board
JTAG_TCK: R26.1, U6.E10 (TCK); also elsewhere on the board
JTAG_TDI: R33.1, U6.E11 (TDI); also elsewhere on the board
JTAG_TDO: U6.E13 (TDO); also elsewhere on the board
JTAG_TMS: R32.1, U6.E12 (TMS); also elsewhere on the board
unnamed: C9.2, D1.3 (A), D3.3 (A), Q3.1 (G), R5.1
unnamed: D2.1 (A1), Q3.3 (D)
unnamed: R11.2, R12.1, U2.6 (FB)
unnamed: L1.1, U2.3 (SW)
unnamed: R13.2, R14.1, U3.6 (FB)
unnamed: L2.1, U3.3 (SW)
unnamed: R15.2, R16.1, U4.6 (FB)
unnamed: L3.1, U4.3 (SW)
unnamed: C85.1, R63.1, U6.K10 (VREFADC_P)
PB_N: Q2.2 (S), R10.1; also elsewhere on the board
PGOOD: R20.1, U4.5 (PG); also elsewhere on the board
PWR_HOLD: D2.2 (A2), R6.2; also elsewhere on the board
RTC_INT_N: Q2.5 (S), R9.1
RTC_SCL: Q1.5 (S), R7.1
RTC_SDA: Q1.2 (S), R8.1
TP_INT_N: Q4.5 (S), R64.1; also elsewhere on the board
VBAT_CELL: R27.1; also elsewhere on the board

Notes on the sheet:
3V3_AO: always-on rail for the RTC and power control
1.8 V auxiliary (VCCA, VCCADC): 0.6 V x (1 + 20k/10k)
Notes 1. 5 V is always present. 3V3_AO is always on; everything else is off in deep sleep. 2. EN_PWR starts U3; each power-good output enables the next converter (UG040012 2.1: follow the data sheet power-up order; core first, I/O last). 3. PGOOD (3V3 in regulation) goes to the FPGA as a supply mon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
1.0 V core (VCC, VCC_DRM): 0.6 V x (1 + 20k/30k)
VCCIOCFG: 47u, 470n, 100n
Gate at +3V3: with the FPGA rail off each FET is off and its body diode is reverse biased, so the always-on side stays high and nothing back-feeds the unpowered FPGA.
Configuration: MODE[2:0] = 001 (master SPI) strapped on the Base sheet; VCCIOCFG = VCCIOL5 = 3.3 V; SCBV tied to VCCIOCFG. JTAG goes to J1 (fixture carrier only; eFuse-locked after enrollment). VCC/VCC_DRM 1.0 V, VCCA 1.8 V, VCCB and VCCADC filtered from 1.8 V on the Base sheet. Core/aux decoupling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
5 V monitor: 0.45 V at VAADC
Start: the carrier button (PB_N_AO) or the RTC /INT pulls PWR_ON_N low, Q2 charges EN_PWR. Power-on: C on PWR_ON_N gives one start pulse when 5V arrives. Run: the boot ROM drives PWR_HOLD high. Sleep: the loader sets the next alarm and drops PWR_HOLD.
XC6206: 1 uA quiescent, 6 V max input.
Isolation between the FPGA (switched 3V3) and the always-on domain
Step-downs, sequenced 1V0 -> 1V8 -> 3V3 through the power-good chain
Power control: EN_PWR = power button | RTC alarm | PWR_HOLD (FPGA)
3.3 V I/O and peripherals: 0.6 V x (1 + 68k/15k) = 3.32 V
Real-time clock: wake alarm, local time (untrusted). Backup cells are external (VBAT_CELL via J1); keep CHGEN = 0.
Load: RTC, pull-ups (uA).

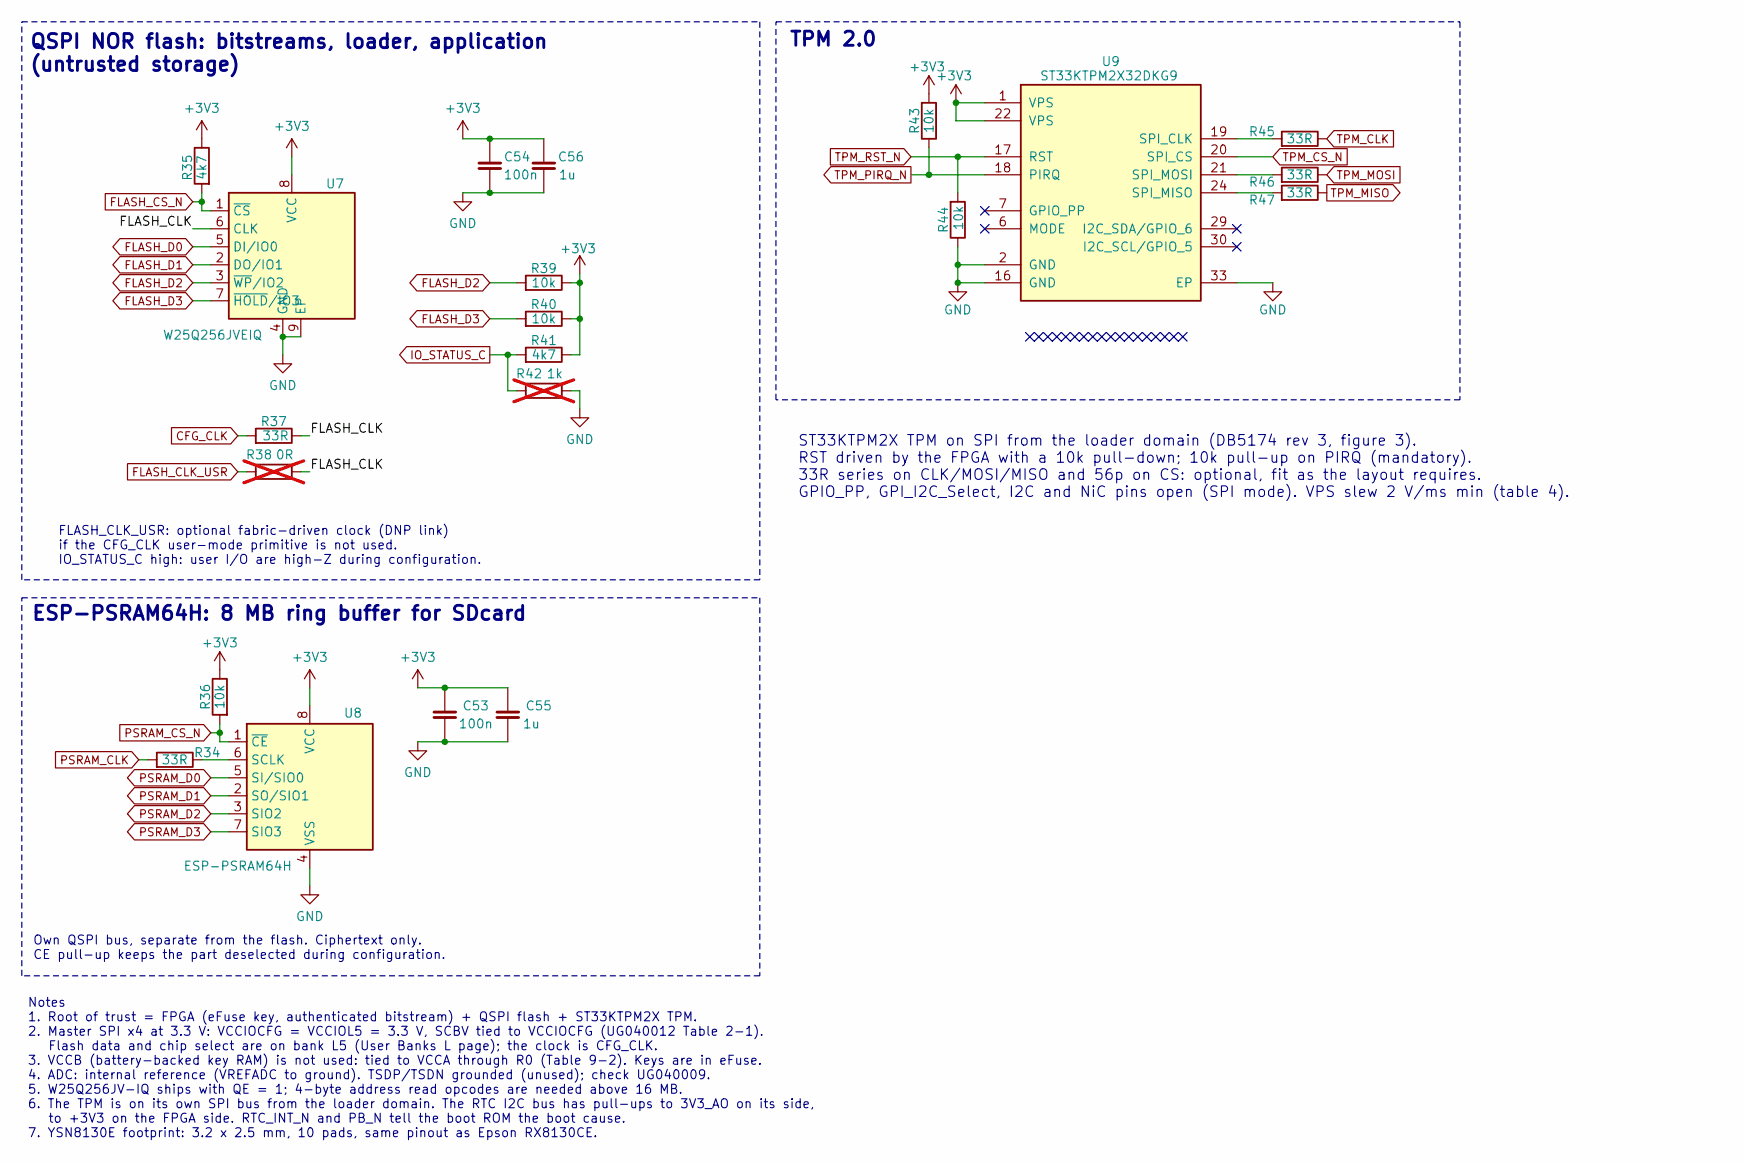
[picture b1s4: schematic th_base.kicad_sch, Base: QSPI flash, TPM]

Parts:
C53, C54: 100n; C_0402_1005Metric; LCSC C1525
C55, C56: 1u; C_0402_1005Metric; LCSC C52923
R34, R37, R45, R46, R47: 33R; R_0402_1005Metric; LCSC C25105
R35, R41: 4k7; R_0402_1005Metric; LCSC C25900
R36, R39, R40, R43, R44: 10k; R_0402_1005Metric; LCSC C25744
R38: 0R; R_0402_1005Metric; LCSC C17168; not fitted
R42: 1k; R_0402_1005Metric; LCSC C11702; not fitted
U7: W25Q256JVEIQ; WSON-8-1EP_8x6mm_P1.27mm_EP3.4x4.3mm; MPN W25Q256JVEIQ; LCSC C97522
U8: ESP-PSRAM64H; SOIC-8_3.9x4.9mm_P1.27mm; MPN ESP-PSRAM64H
U9: ST33KTPM2X32DKG9; QFN-32-1EP_5x5mm_P0.5mm_EP3.6x3.6mm; MPN ST33KTPM2X32DKG9

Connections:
/Flash. PSRAM/FLASH_CLK: R37.2, R38.2, U7.6 (CLK)
CFG_CLK: R37.1; also elsewhere on the board
FLASH_CLK_USR: R38.1; also elsewhere on the board
FLASH_CS_N: R35.1, U7.1 (~CS); also elsewhere on the board
FLASH_D0: U7.5 (DI/IO0); also elsewhere on the board
FLASH_D1: U7.2 (DO/IO1); also elsewhere on the board
FLASH_D2: R39.1, U7.3 (~WP/IO2); also elsewhere on the board
FLASH_D3: R40.1, U7.7 (~HOLD/IO3); also elsewhere on the board
GND: C53.2, C54.2, C55.2, C56.2, R42.2, R44.2, U7.4 (GND), U7.9 (EP), U8.4 (VSS), U9.2 (GND), U9.16 (GND), U9.33 (EP); also elsewhere on the board
IO_STATUS_C: R41.1, R42.1; also elsewhere on the board
unnamed: R34.2, U8.6 (SCLK)
unnamed: R45.1, U9.19 (SPI_CLK)
unnamed: R47.1, U9.24 (SPI_MISO)
unnamed: R46.1, U9.21 (SPI_MOSI)
PSRAM_CLK: R34.1
PSRAM_CS_N: R36.1, U8.1 (~CE)
PSRAM_D0: U8.5 (SI/SIO0)
PSRAM_D1: U8.2 (SO/SIO1)
PSRAM_D2: U8.3 (SIO2)
PSRAM_D3: U8.7 (SIO3)
TPM_CLK: R45.2
TPM_CS_N: U9.20 (SPI_CS)
TPM_MISO: R47.2
TPM_MOSI: R46.2
TPM_PIRQ_N: R43.2, U9.18 (PIRQ); also elsewhere on the board
TPM_RST_N: R44.1, U9.17 (RST); also elsewhere on the board

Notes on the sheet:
Own QSPI bus, separate from the flash. Ciphertext only. CE pull-up keeps the part deselected during configuration.
ST33KTPM2X TPM on SPI from the loader domain (DB5174 rev 3, figure 3). RST driven by the FPGA with a 10k pull-down; 10k pull-up on PIRQ (mandatory). 33R series on CLK/MOSI/MISO and 56p on CS: optional, fit as the layout requires. GPIO_PP, GPI_I2C_Select, I2C and NiC pins open (SPI mode). VPS slew 2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
ESP-PSRAM64H: 8 MB ring buffer for SDcard
Notes 1. Root of trust = FPGA (eFuse key, authenticated bitstream) + QSPI flash + ST33KTPM2X TPM. 2. Master SPI x4 at 3.3 V: VCCIOCFG = VCCIOL5 = 3.3 V, SCBV tied to VCCIOCFG (UG040012 Table 2-1). Flash data and chip select are on bank L5 (User Banks L page); the clock is CFG_CLK. 3. VCCB (battery-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
FLASH_CLK_USR: optional fabric-driven clock (DNP link) if the CFG_CLK user-mode primitive is not used. IO_STATUS_C high: user I/O are high-Z during configuration.
TPM 2.0
QSPI NOR flash: bitstreams, loader, application (untrusted storage)
